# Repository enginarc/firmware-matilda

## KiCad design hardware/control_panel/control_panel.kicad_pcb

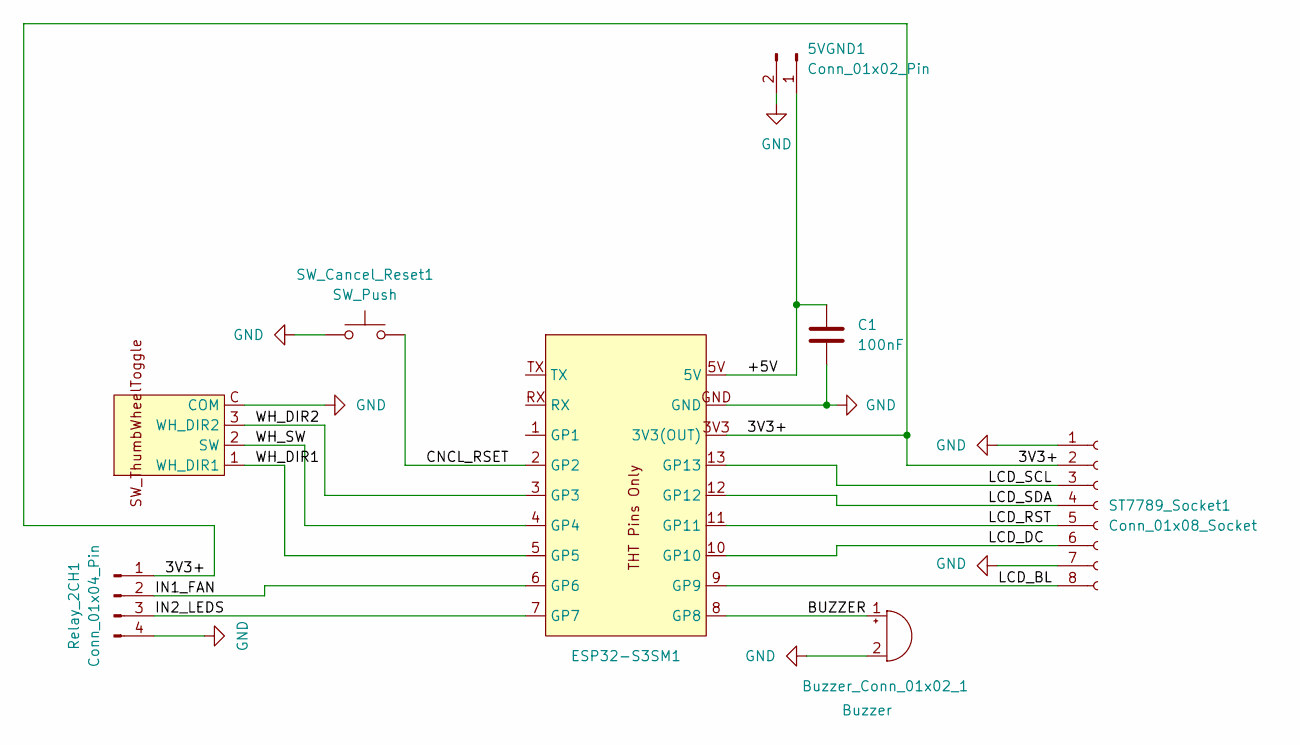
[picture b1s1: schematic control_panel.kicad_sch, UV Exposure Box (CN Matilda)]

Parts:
5VGND1: Conn_01x02_Pin; JST_XH_B2B-XH-A_1x02_P2.50mm_Vertical
Buzzer_Conn_01x02_1: Buzzer; JST_XH_B2B-XH-A_1x02_P2.50mm_Vertical
C1: 100nF; C_Disc_D6.0mm_W2.5mm_P5.00mm
ESP32-S3SM1: ESP32-S3_Super_Mini_THTONLY_(B.Cu)
Relay_2CH1: Conn_01x04_Pin; JST_XH_B4B-XH-A_1x04_P2.50mm_Vertical
ST7789_Socket1: Conn_01x08_Socket; PinSocket_1x08_P2.54mm_Horizontal
SW_Cancel_Reset1: SW_Push; SW_PUSH_6mm_H8.5mm
SW_TWT_Start_Pause_Adjust1: SW_ThumbWheelToggle

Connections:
/3V3+: ESP32-S3SM1.3V3 (3V3(OUT)), Relay_2CH1.1, ST7789_Socket1.2
/+5V: 5VGND1.1, C1.1, ESP32-S3SM1.5V
/BUZZER: Buzzer_Conn_01x02_1.1 (+), ESP32-S3SM1.8 (GP8)
/CNCL_RSET: ESP32-S3SM1.2 (GP2), SW_Cancel_Reset1.2
/IN1_FAN: ESP32-S3SM1.6 (GP6), Relay_2CH1.2
/IN2_LEDS: ESP32-S3SM1.7 (GP7), Relay_2CH1.3
/LCD_BL: ESP32-S3SM1.9 (GP9), ST7789_Socket1.8
/LCD_DC: ESP32-S3SM1.10 (GP10), ST7789_Socket1.6
/LCD_RST: ESP32-S3SM1.11 (GP11), ST7789_Socket1.5
/LCD_SCL: ESP32-S3SM1.13 (GP13), ST7789_Socket1.3
/LCD_SDA: ESP32-S3SM1.12 (GP12), ST7789_Socket1.4
/WH_DIR1: ESP32-S3SM1.5 (GP5), SW_TWT_Start_Pause_Adjust1.1 (WH_DIR1)
/WH_DIR2: ESP32-S3SM1.3 (GP3), SW_TWT_Start_Pause_Adjust1.3 (WH_DIR2)
/WH_SW: ESP32-S3SM1.4 (GP4), SW_TWT_Start_Pause_Adjust1.2 (SW)
GND: 5VGND1.2, Buzzer_Conn_01x02_1.2 (-), C1.2, ESP32-S3SM1.GND, Relay_2CH1.4, ST7789_Socket1.1, ST7789_Socket1.7, SW_Cancel_Reset1.1, SW_TWT_Start_Pause_Adjust1.C (COM)

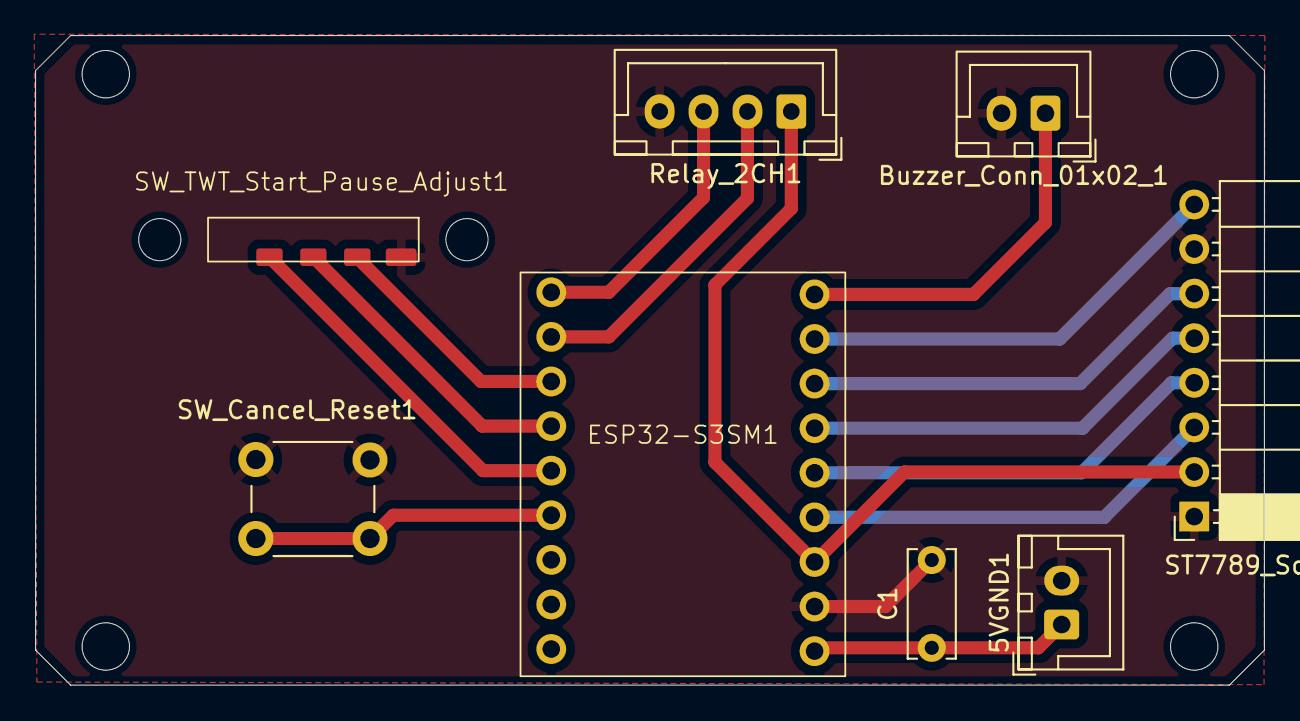
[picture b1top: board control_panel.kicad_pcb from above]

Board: 2 copper layers, 70.0 x 37.0 mm, 8 parts (0 on the bottom side), 15 nets.

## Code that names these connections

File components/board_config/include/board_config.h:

#pragma once

#ifdef __cplusplus
extern "C" {
#endif

#include "driver/spi_master.h"
#include "driver/gpio.h"

// --- ST7789 Display (Hardware SPI) ---
#define LCD_HOST    SPI2_HOST
#define PIN_LCD_SCLK (gpio_num_t)13
#define PIN_LCD_MOSI (gpio_num_t)12
#define PIN_LCD_RST (gpio_num_t)11
#define PIN_LCD_DC  (gpio_num_t)10
#define PIN_LCD_CS       -1             // Tied to GND on most Super Mini modules
#define PIN_LCD_BL  (gpio_num_t)9  // PWM capable

#define LCD_H_RES        240
#define LCD_V_RES        320
#define LCD_PIXEL_CLOCK  (40 * 1000 * 1000) // 40MHz

// --- Relays (2-Channel Module) ---
#define PIN_RELAY_FAN (gpio_num_t)6  // Relay 2: Cooling Fan
#define PIN_RELAY_LED (gpio_num_t)7  // Relay 1: UV LEDs

// --- Input & Feedback ---
#define PIN_BUZZER       (gpio_num_t)8
#define PIN_RESERVED     (gpio_num_t)1

#define PIN_BTN_CNCL_RST   (gpio_num_t)2

#define PIN_TWT_DIR1        (gpio_num_t)5
#define PIN_TWT_SW       (gpio_num_t)4 // TWT Switch (Timer Nob click)
#define PIN_TWT_DIR2        (gpio_num_t)3

void board_init_gpio();

#ifdef __cplusplus
}
#endif

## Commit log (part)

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2026-01-19 Initial
2026-01-19 gitignore updates
2026-01-19 EC11 and worflow updates
2026-01-19 PIN pre-pcb
2026-01-19 revisions for workflow
2026-01-19 revisions to EC11 handling
2026-01-19 workflow v1
2026-01-19 revisions to workflow
2026-01-19 implementation of revised workflow
2026-01-19 cleanup after impl revised workflow
2026-01-20 MC PIN revisions for KiCad
2026-01-22 KiCad updates and EC11 to TWT
2026-01-22 Thumb wheel toggle switch implementation
2026-01-24 KiCad and python script for stitching PCB layers into one SVG for printing
2026-01-24 kicad pcb export - change print helper application
2026-02-11 KiCad design fixes and Kicad pcb export fixes
2026-02-12 Minimum vias - 0.3mm tracks
2026-02-13 Kicad - Mimimum Vias + 0.5mm min track width + script changes
2026-02-22 KiCad changes
2026-02-22 KiCad - ESP32-S3 Super Mini B.Cu - Fix for flipped connections
2026-02-22 Reflect KiCad changes to board_config
2026-02-22 Fix: LCD SCL SDA mixup
2026-02-23 KiCad changes for mountholes
2026-02-23 KiCad changes for Control Panel PCB Mountholes
2026-03-04 Add "layer" parameter to limit export to F.cu or B.cu layers
2026-03-21 Add argument --copies
2026-03-21 Add --orient argument
2026-03-21 Fix KiCad command line argument
